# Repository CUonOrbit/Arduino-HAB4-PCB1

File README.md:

View this project on [CADLAB.io](https://cadlab.io/project/30359). 

# Arduino-HAB4-PCB1

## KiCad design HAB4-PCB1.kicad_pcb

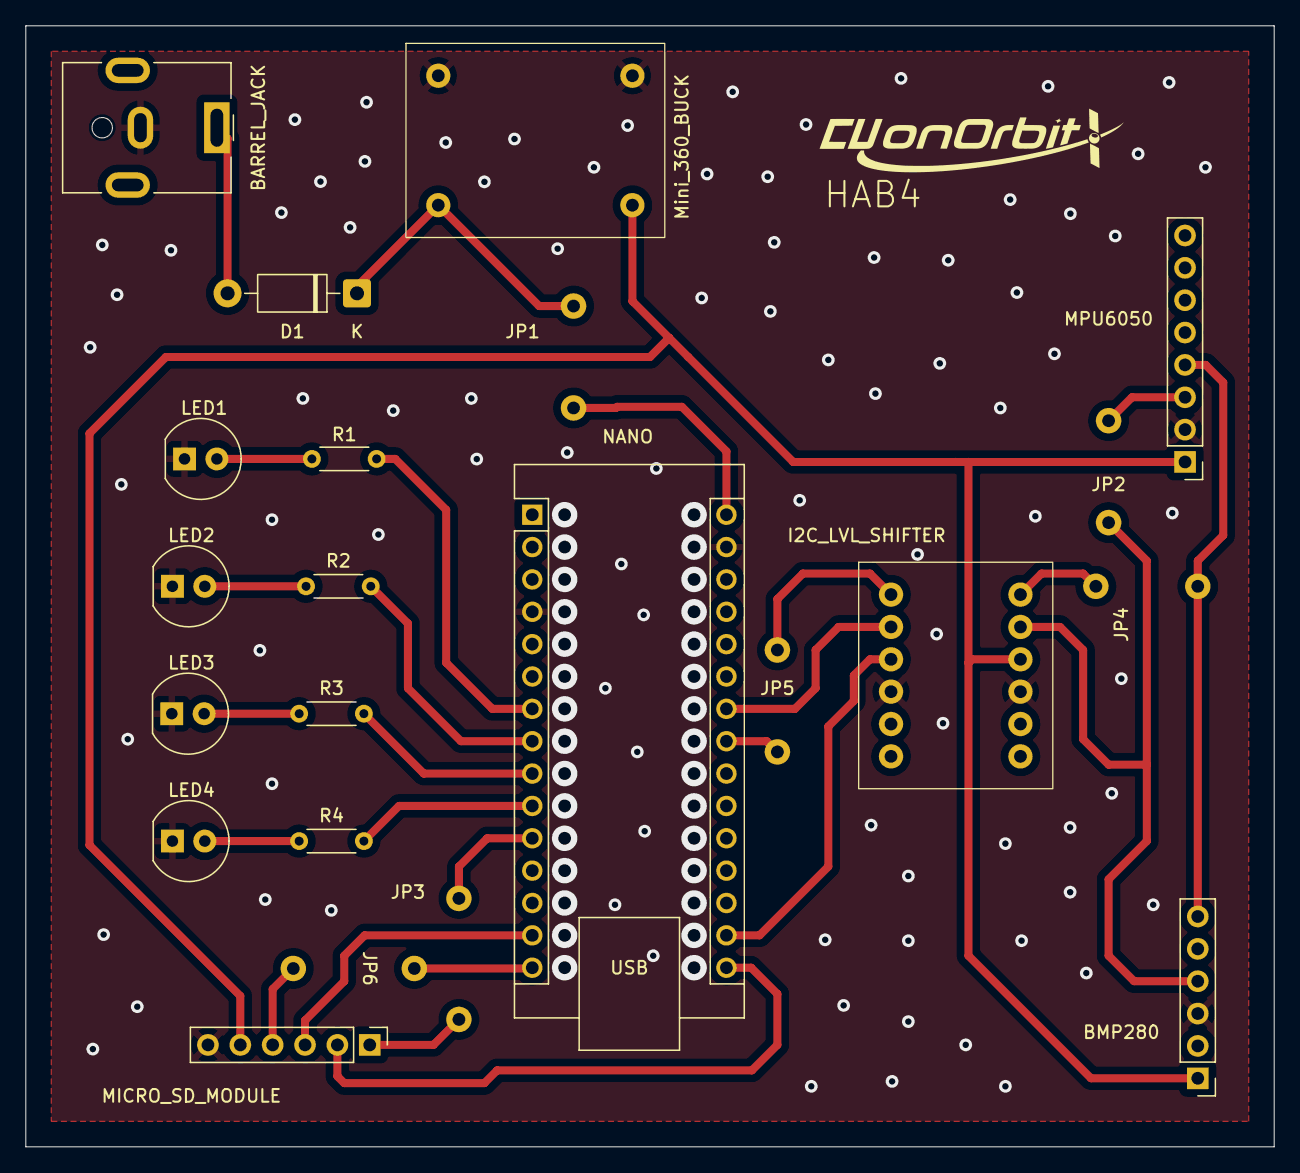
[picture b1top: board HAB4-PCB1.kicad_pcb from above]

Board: 2 copper layers, 98.0 x 88.0 mm, 22 parts (0 on the bottom side), 27 nets.

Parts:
BARREL_JACK: Barrel_Jack_Switch; BarrelJack_CUI_PJ-063AH_Horizontal
BMP280: Conn_01x06; PinHeader_1x06_P2.54mm_Vertical
D1: 1N5819; D_DO-41_SOD81_P10.16mm_Horizontal
D2, D3, D4, D5: LED; JCLPCB_THT_LED_D5.0mm
I2C_LVL_SHIFTER: Conn_01x12; I2C_LogicLevelConverter
JP1, JP2, JP4, JP5: Jumper_2_Bridged; 6mm_jumper
JP3, JP6: Jumper_2_Bridged; 8mm_jumper
MICRO_SD_MODULE: Conn_01x06; PinHeader_1x06_P2.54mm_Vertical
MPU6050: Conn_01x08; PinHeader_1x08_P2.54mm_Vertical
Mini_360_BUCK: Conn_01x04; Buck_Module_4pin_12.7x17.78mm
NANO: Arduino_Nano_v3.x; Arduino_Nano
R1, R2, R4: R; R_Axial_DIN0204_L3.6mm_D1.6mm_P5.08mm_Horizontal
R3: R3; R_Axial_DIN0204_L3.6mm_D1.6mm_P5.08mm_Horizontal

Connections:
+9V: BARREL_JACK.1, D1.2 (A)
GND: BARREL_JACK.2, BMP280.3 (GND), D2.1 (K), D3.1 (K), D4.1 (K), D5.1 (K), I2C_LVL_SHIFTER.4 (GND), I2C_LVL_SHIFTER.10 (GND), MICRO_SD_MODULE.6 (GND), MPU6050.2 (GND), Mini_360_BUCK.1 (IN-), Mini_360_BUCK.3 (OUT-), NANO.4 (GND), NANO.29 (GND)
unnamed: BMP280.4 (SCK), I2C_LVL_SHIFTER.2 (HV2), JP2.1 (A)
unnamed: BMP280.6 (SDI), JP4.2 (B), MPU6050.4 (SDA)
unnamed: BMP280.1 (VIN), I2C_LVL_SHIFTER.3 (HV), MICRO_SD_MODULE.5 (VCC), MPU6050.1 (VCC), Mini_360_BUCK.4 (OUT+)
unnamed: D1.1 (K), JP1.1 (A), Mini_360_BUCK.2 (IN+)
unnamed: D2.2 (A), R1.1
unnamed: D3.2 (A), R2.2
unnamed: D4.2 (A), R3.2
unnamed: D5.2 (A), R4.2
unnamed: I2C_LVL_SHIFTER.1 (HV1), JP4.1 (A)
unnamed: I2C_LVL_SHIFTER.7 (LV1), JP5.1 (A)
unnamed: I2C_LVL_SHIFTER.8 (LV2), NANO.24 (A5)
unnamed: I2C_LVL_SHIFTER.9 (LV), NANO.17 (3V3)
unnamed: JP1.2 (B), NANO.30 (VIN)
unnamed: JP2.2 (B), MPU6050.3 (SCL)
unnamed: JP3.1 (A), NANO.11 (D8)
unnamed: JP3.2 (B), MICRO_SD_MODULE.1 (CS)
unnamed: JP5.2 (B), NANO.23 (A4)
unnamed: JP6.1 (A), NANO.15 (D12)
unnamed: JP6.2 (B), MICRO_SD_MODULE.4 (MISO)
unnamed: MICRO_SD_MODULE.3 (MOSI), NANO.14 (D11)
unnamed: MICRO_SD_MODULE.2 (SCK), NANO.16 (D13)
unnamed: NANO.7 (D4), R1.2
unnamed: NANO.8 (D5), R2.1
unnamed: NANO.9 (D6), R3.1
unnamed: NANO.10 (D7), R4.1

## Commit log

2026-05-19 fix ignore
2026-05-19 Backlink to CADLAB.io has been added.
2026-05-23 Connected modules
2026-05-26 footprints and connections update
2026-05-29 pcb traces and remove relay
2026-05-29 gnd plane
2026-05-29 nano GND connect
2026-05-29 board outline and fix GND pins
2026-05-31 Improve GND and fix Shifter pins
2026-06-02 Jumper cables and other
2026-06-04 grounding flood plane
2026-06-05 final changes
